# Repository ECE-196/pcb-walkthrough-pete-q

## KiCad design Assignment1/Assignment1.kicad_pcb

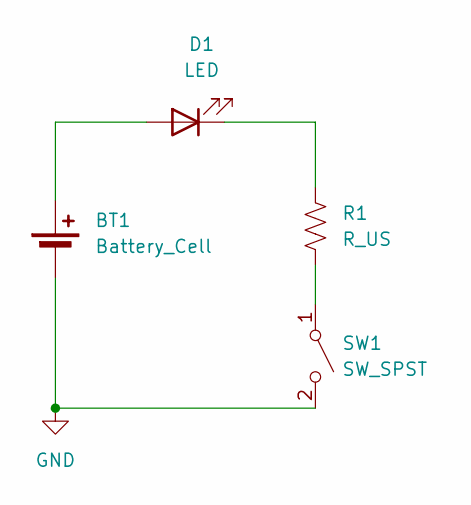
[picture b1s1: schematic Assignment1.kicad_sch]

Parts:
BT1: Battery_Cell; BatteryHolder_Keystone_103_1x20mm
D1: LED; LED_2512_6332Metric
R1: R_US; R_2512_6332Metric
SW1: SW_SPST; SW_Push_1P1T_NO_6x6mm_H9.5mm

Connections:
GND: BT1.2 (-), SW1.2 (B)
unnamed: BT1.1 (+), D1.2 (A)
unnamed: D1.1 (K), R1.1
unnamed: R1.2, SW1.1 (A)

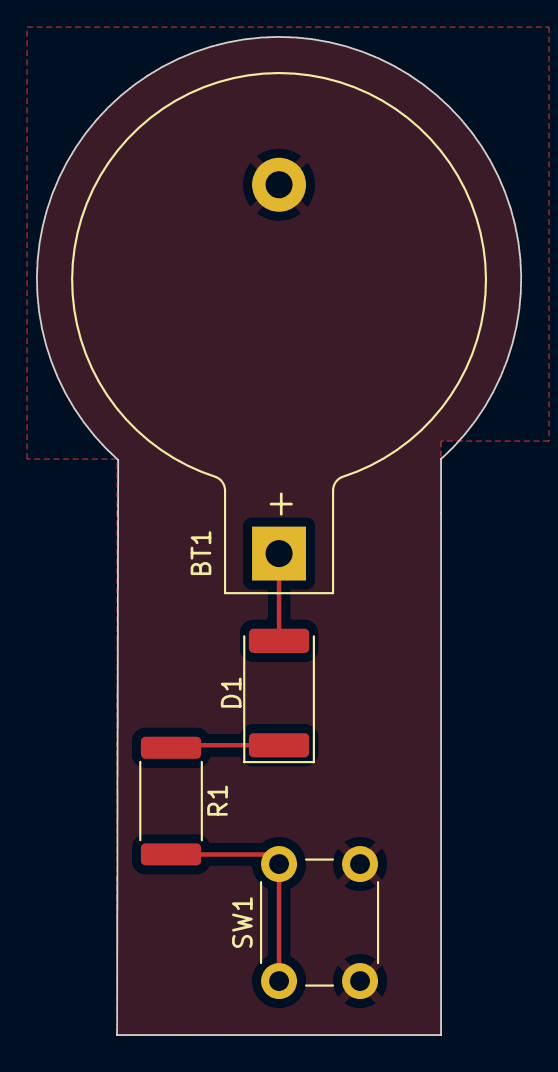
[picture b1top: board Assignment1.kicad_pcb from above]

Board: 2 copper layers, 26.9 x 55.5 mm, 4 parts (0 on the bottom side), 4 nets.

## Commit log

2024-10-07 add deadline
2024-10-08 Added schematic to PCB Editor
2024-10-08 All PNG files added
2024-10-10 Finished
